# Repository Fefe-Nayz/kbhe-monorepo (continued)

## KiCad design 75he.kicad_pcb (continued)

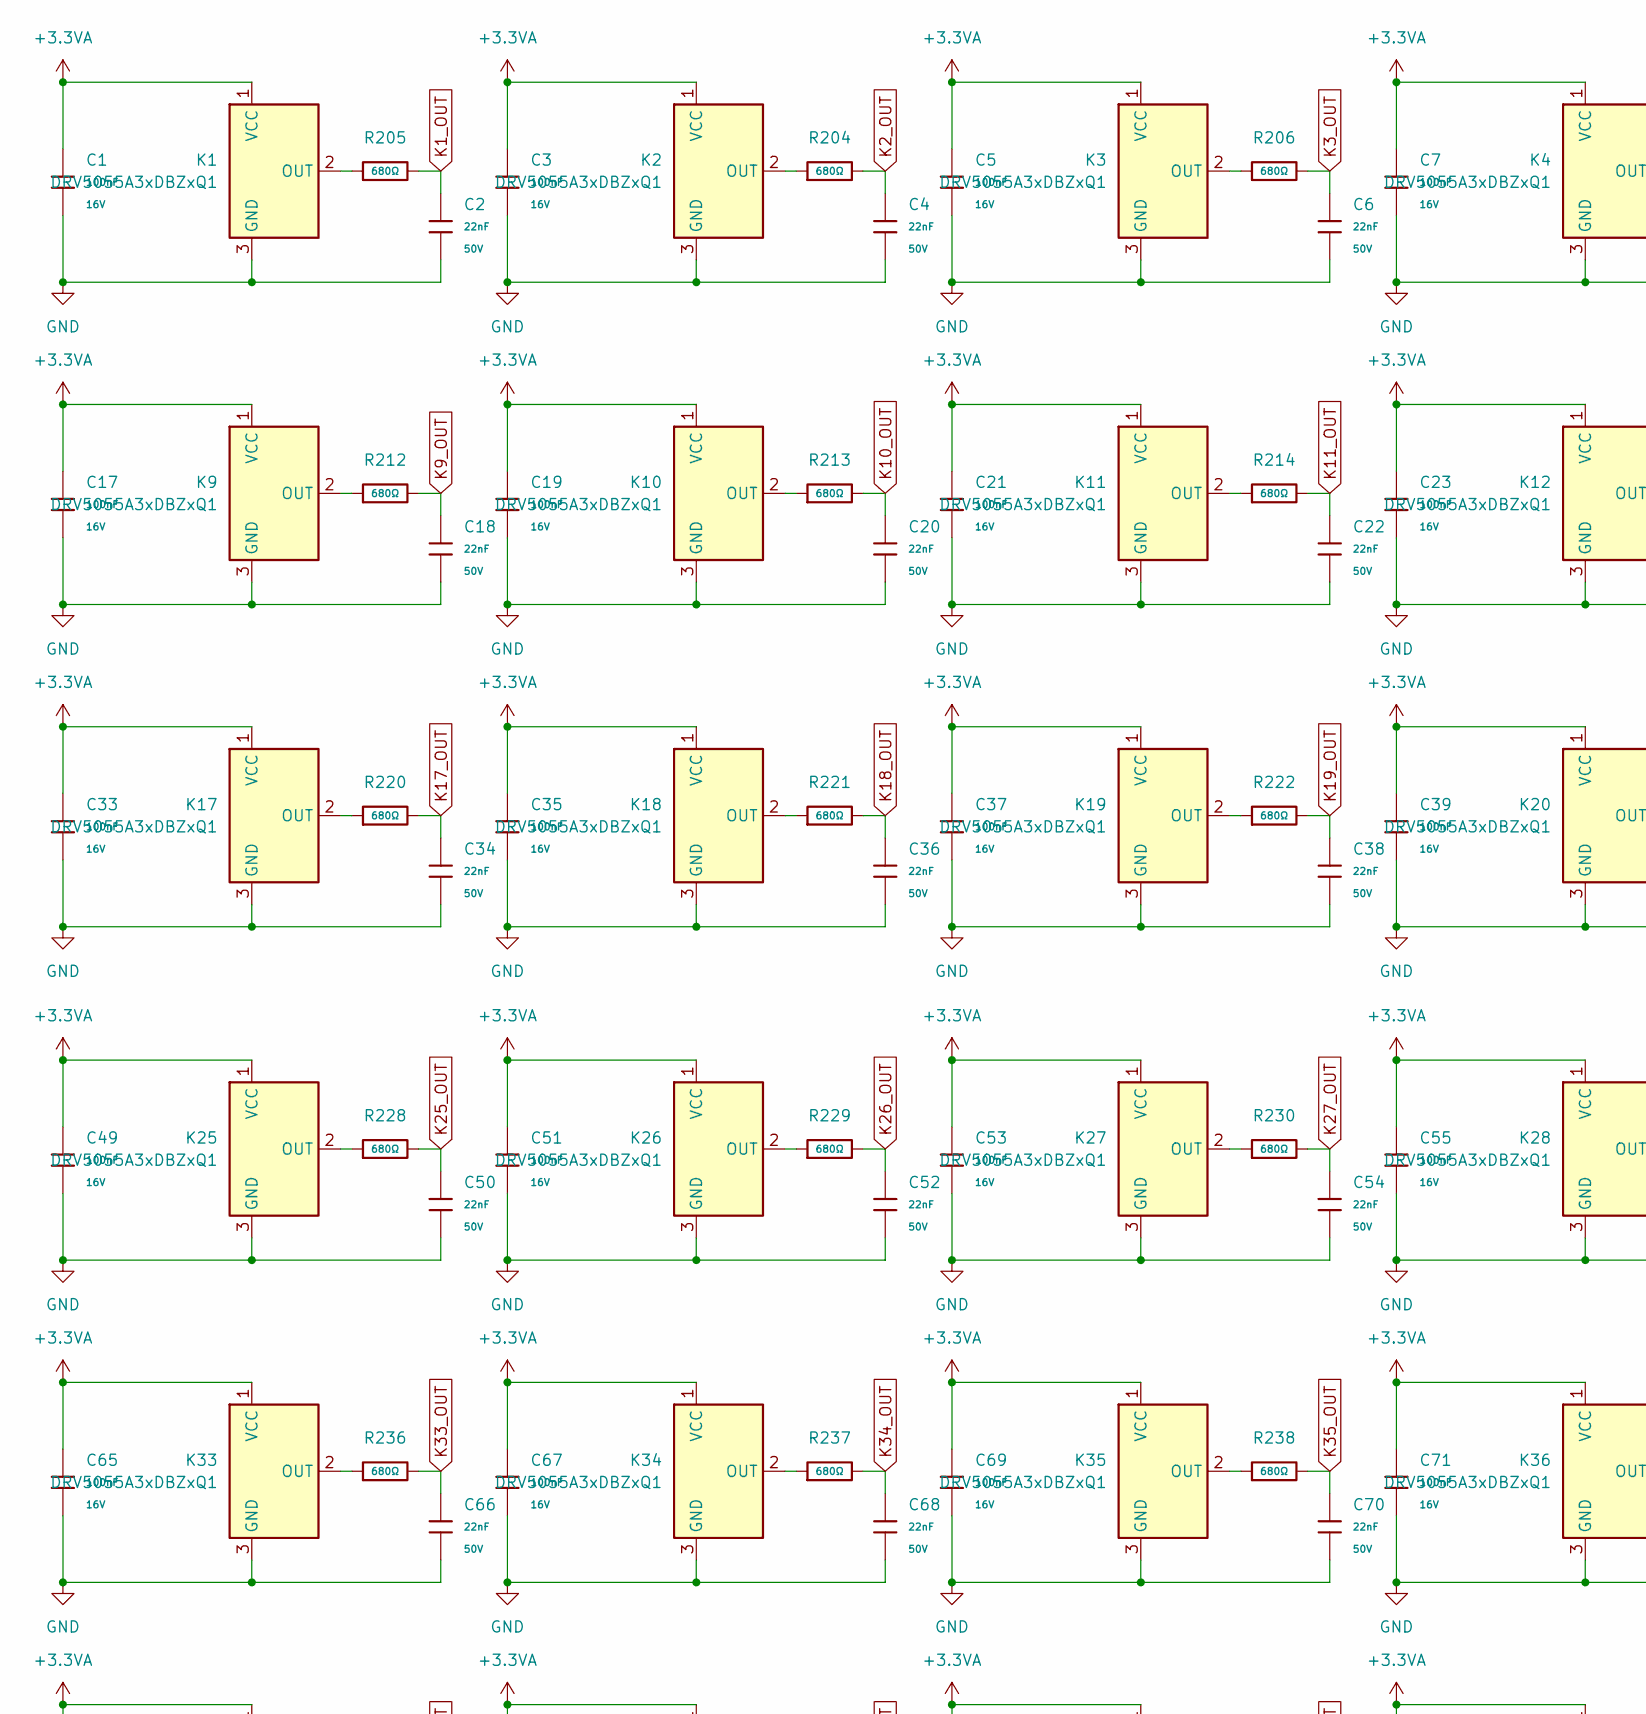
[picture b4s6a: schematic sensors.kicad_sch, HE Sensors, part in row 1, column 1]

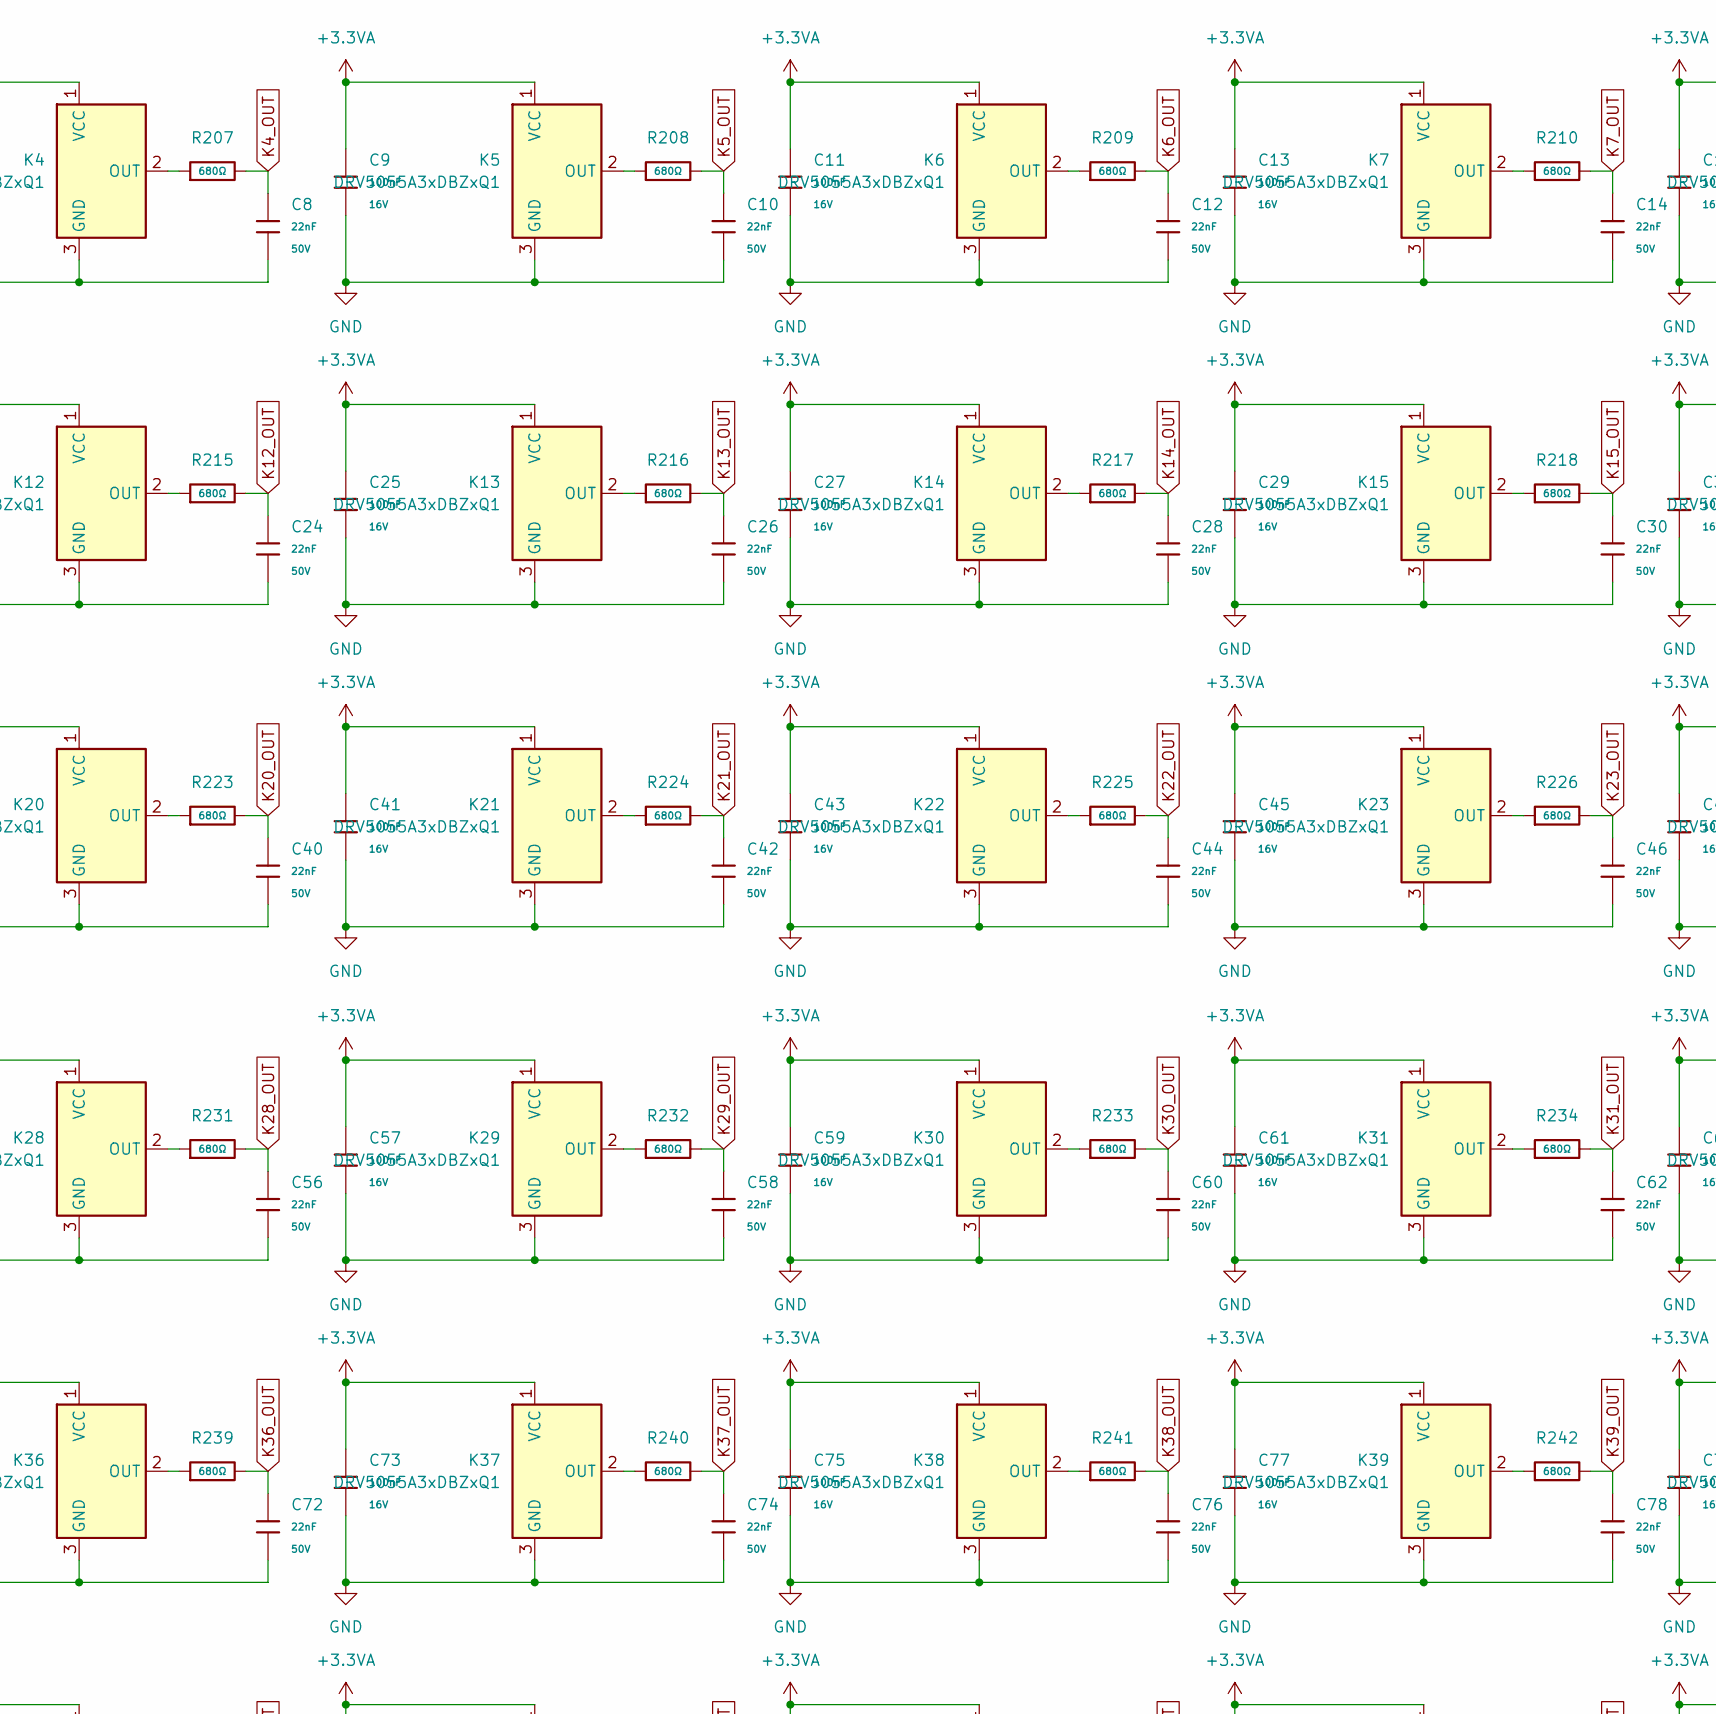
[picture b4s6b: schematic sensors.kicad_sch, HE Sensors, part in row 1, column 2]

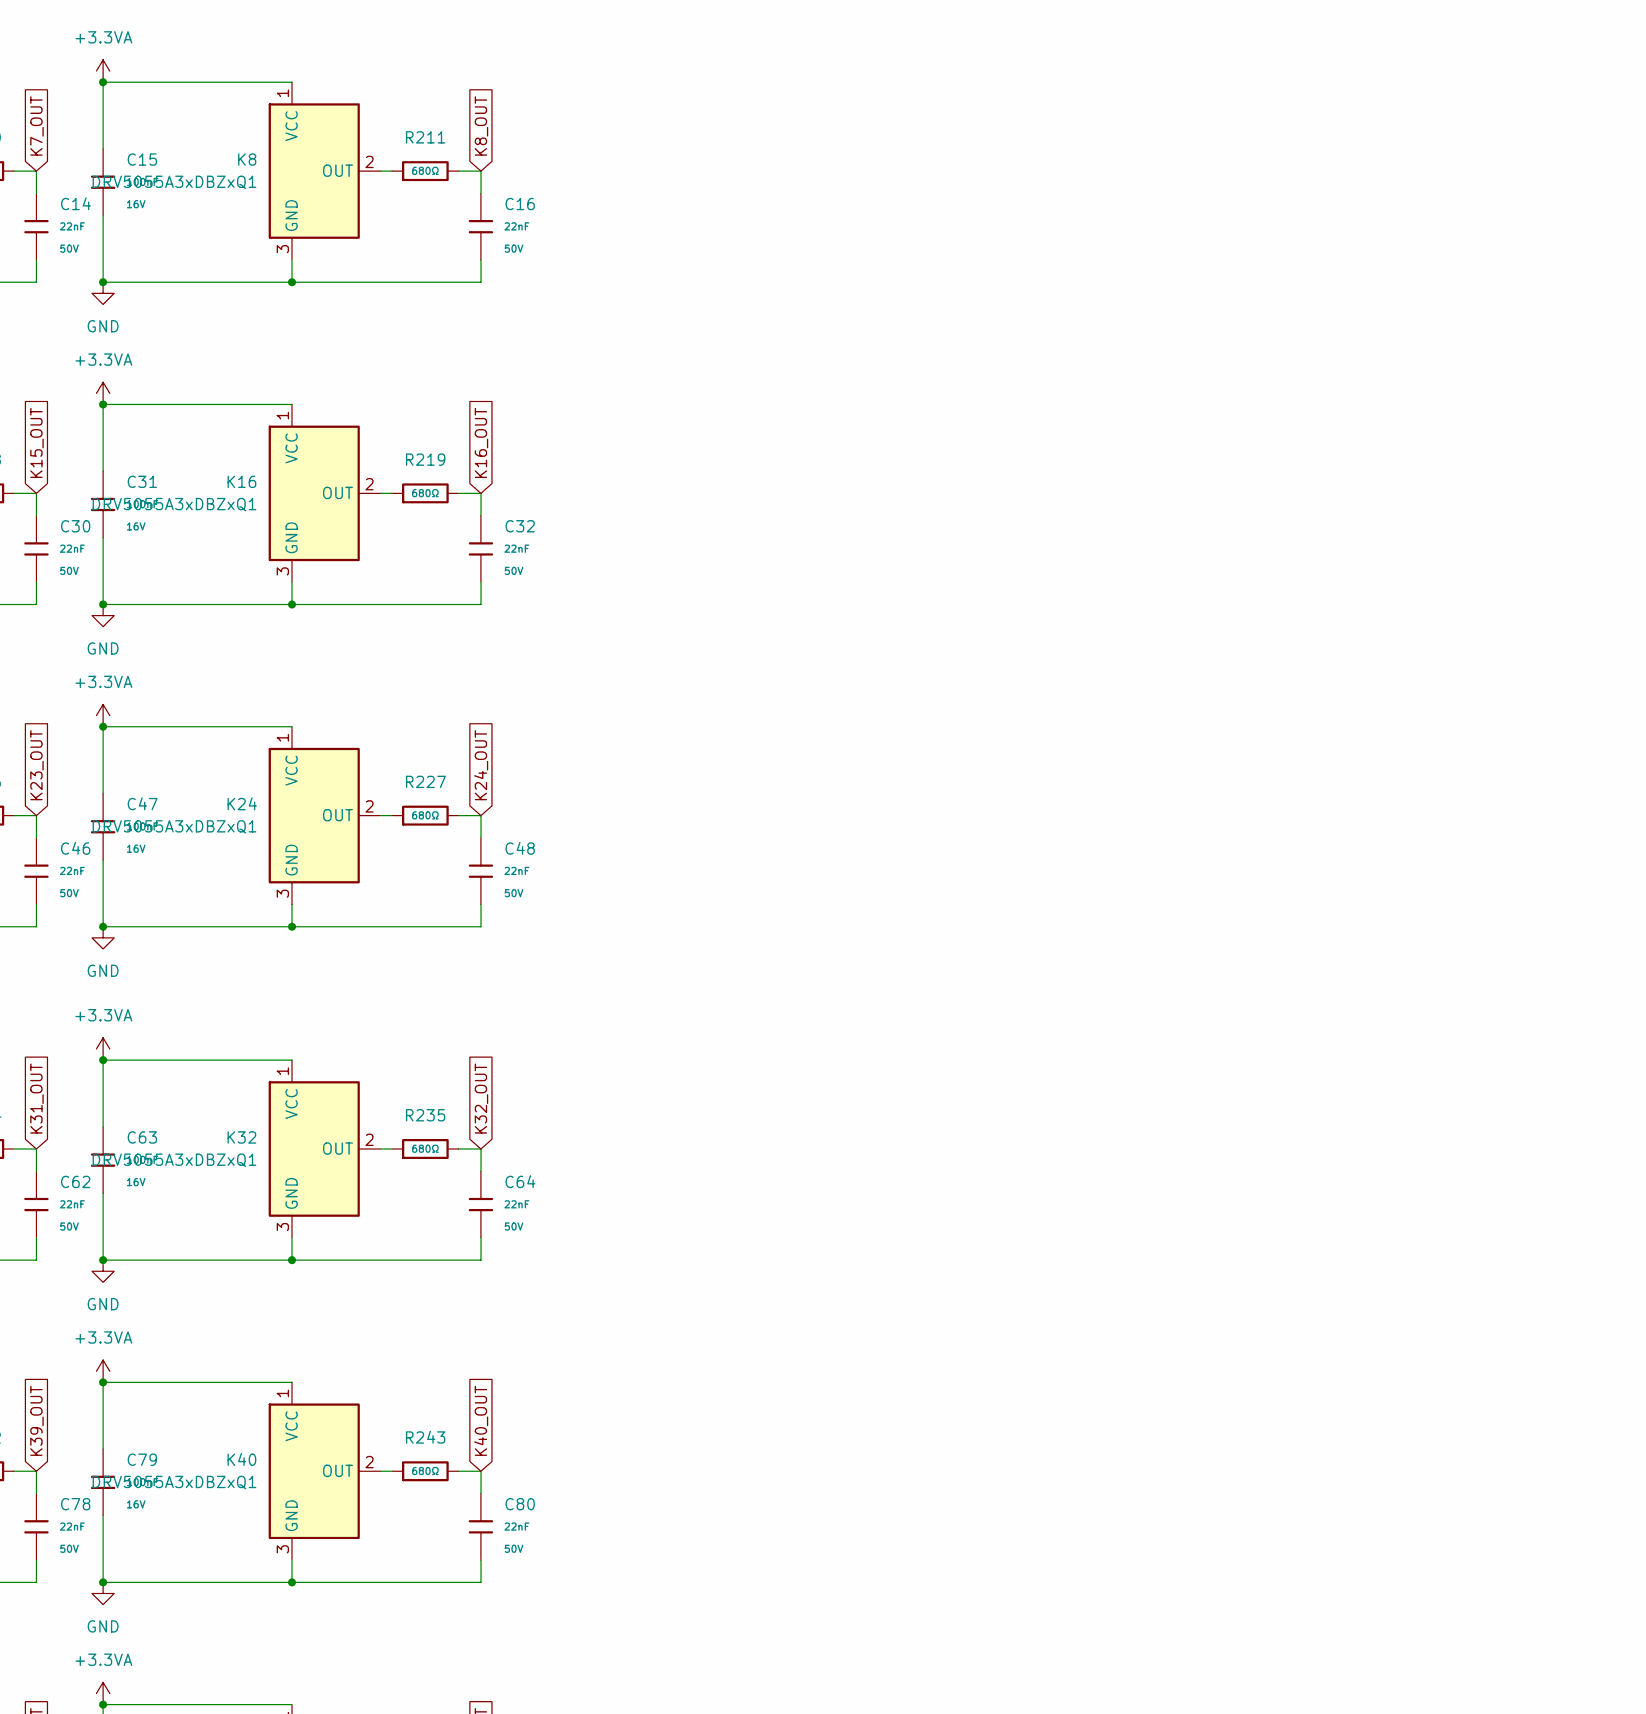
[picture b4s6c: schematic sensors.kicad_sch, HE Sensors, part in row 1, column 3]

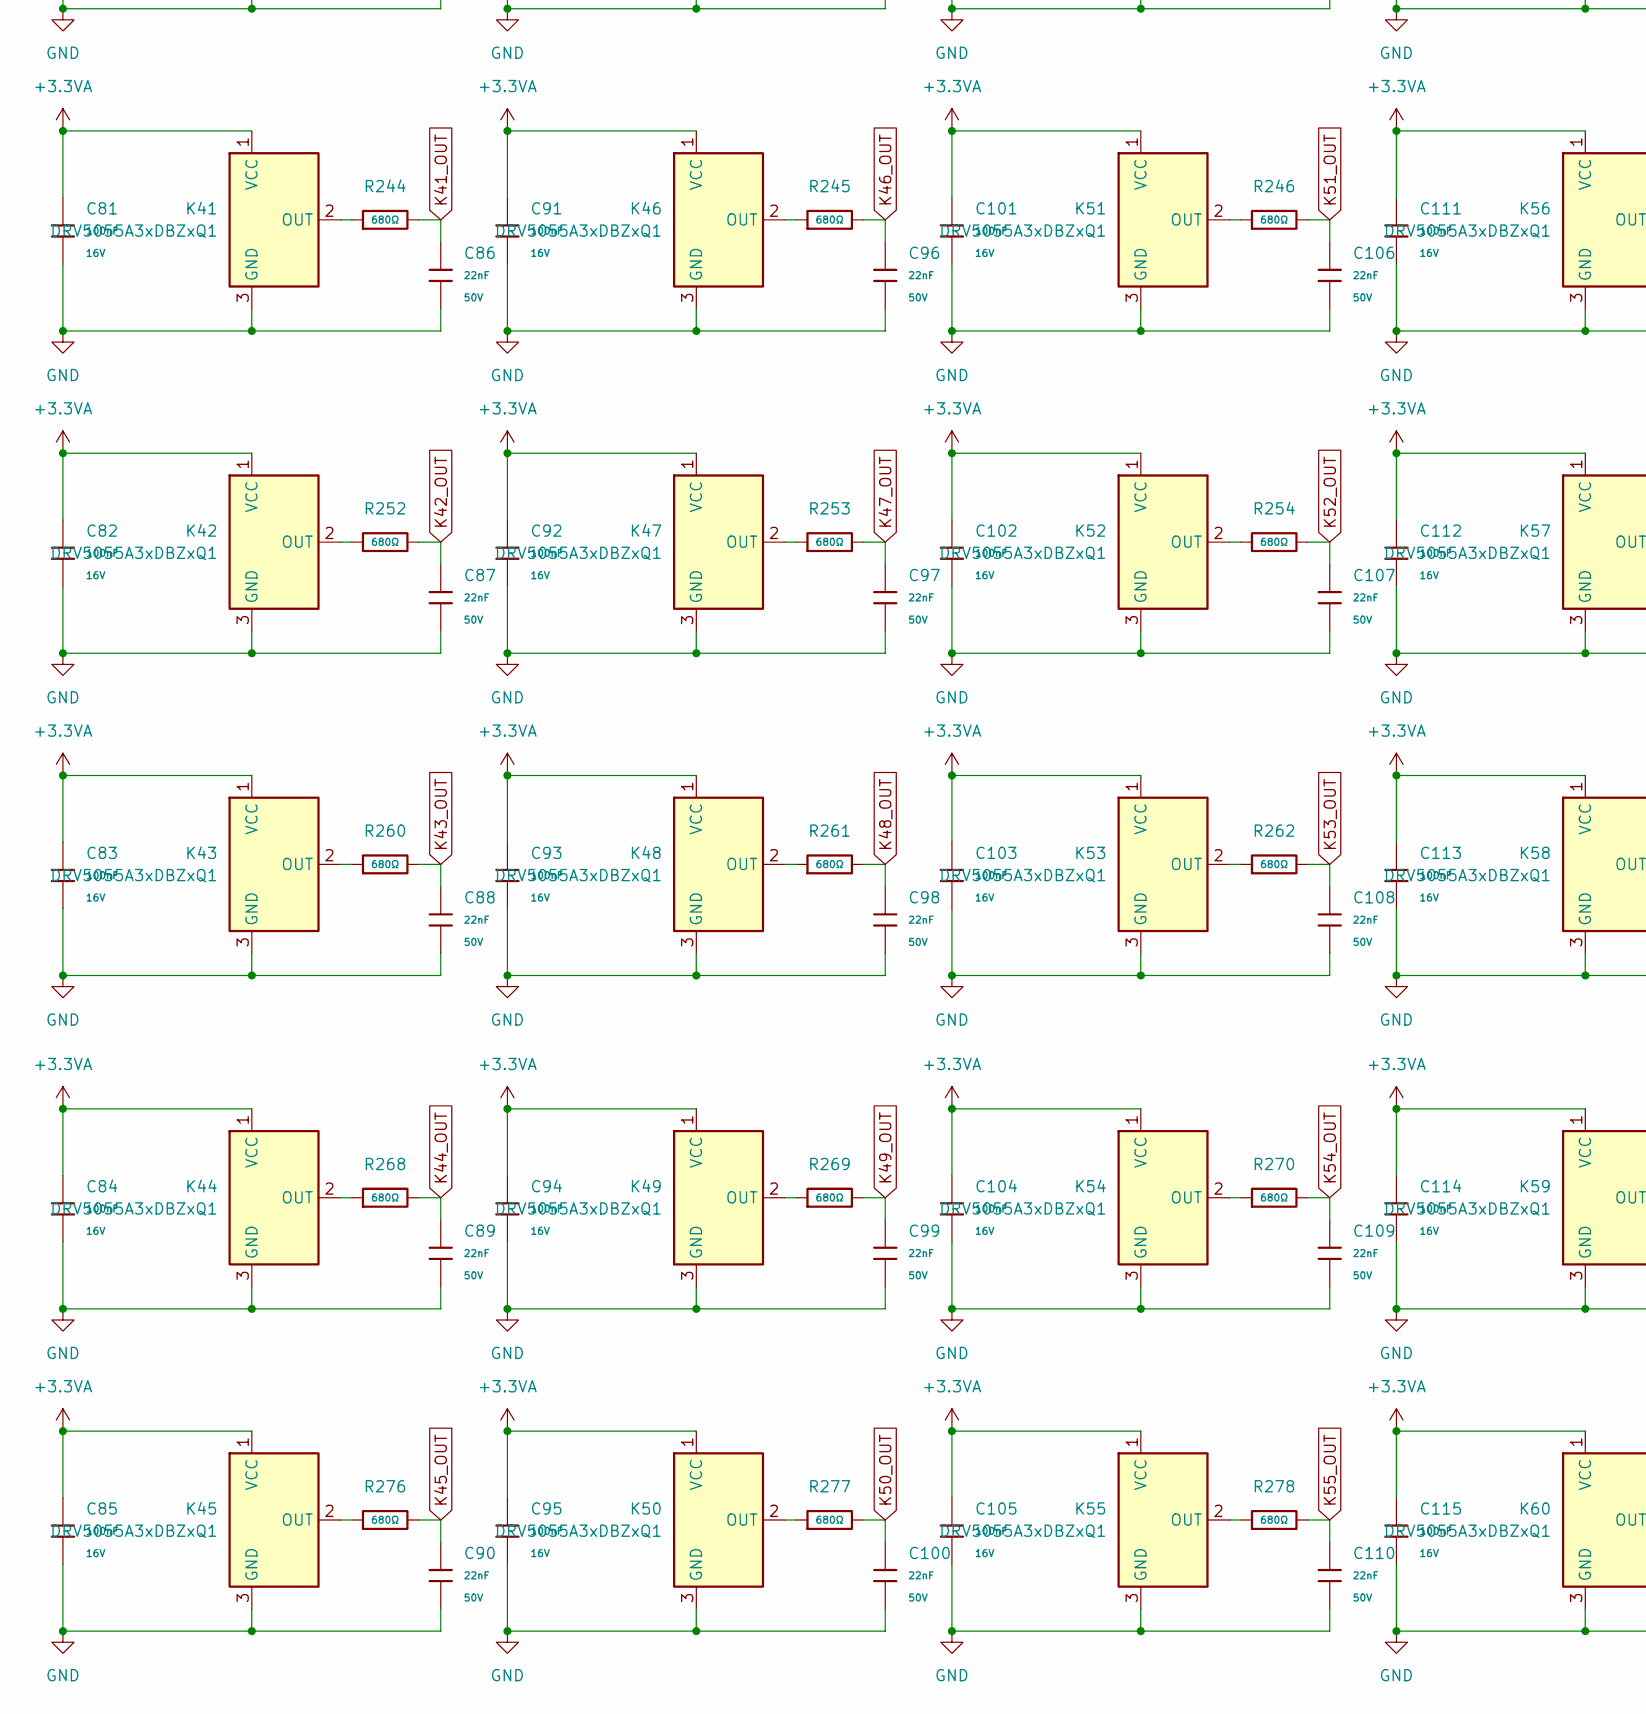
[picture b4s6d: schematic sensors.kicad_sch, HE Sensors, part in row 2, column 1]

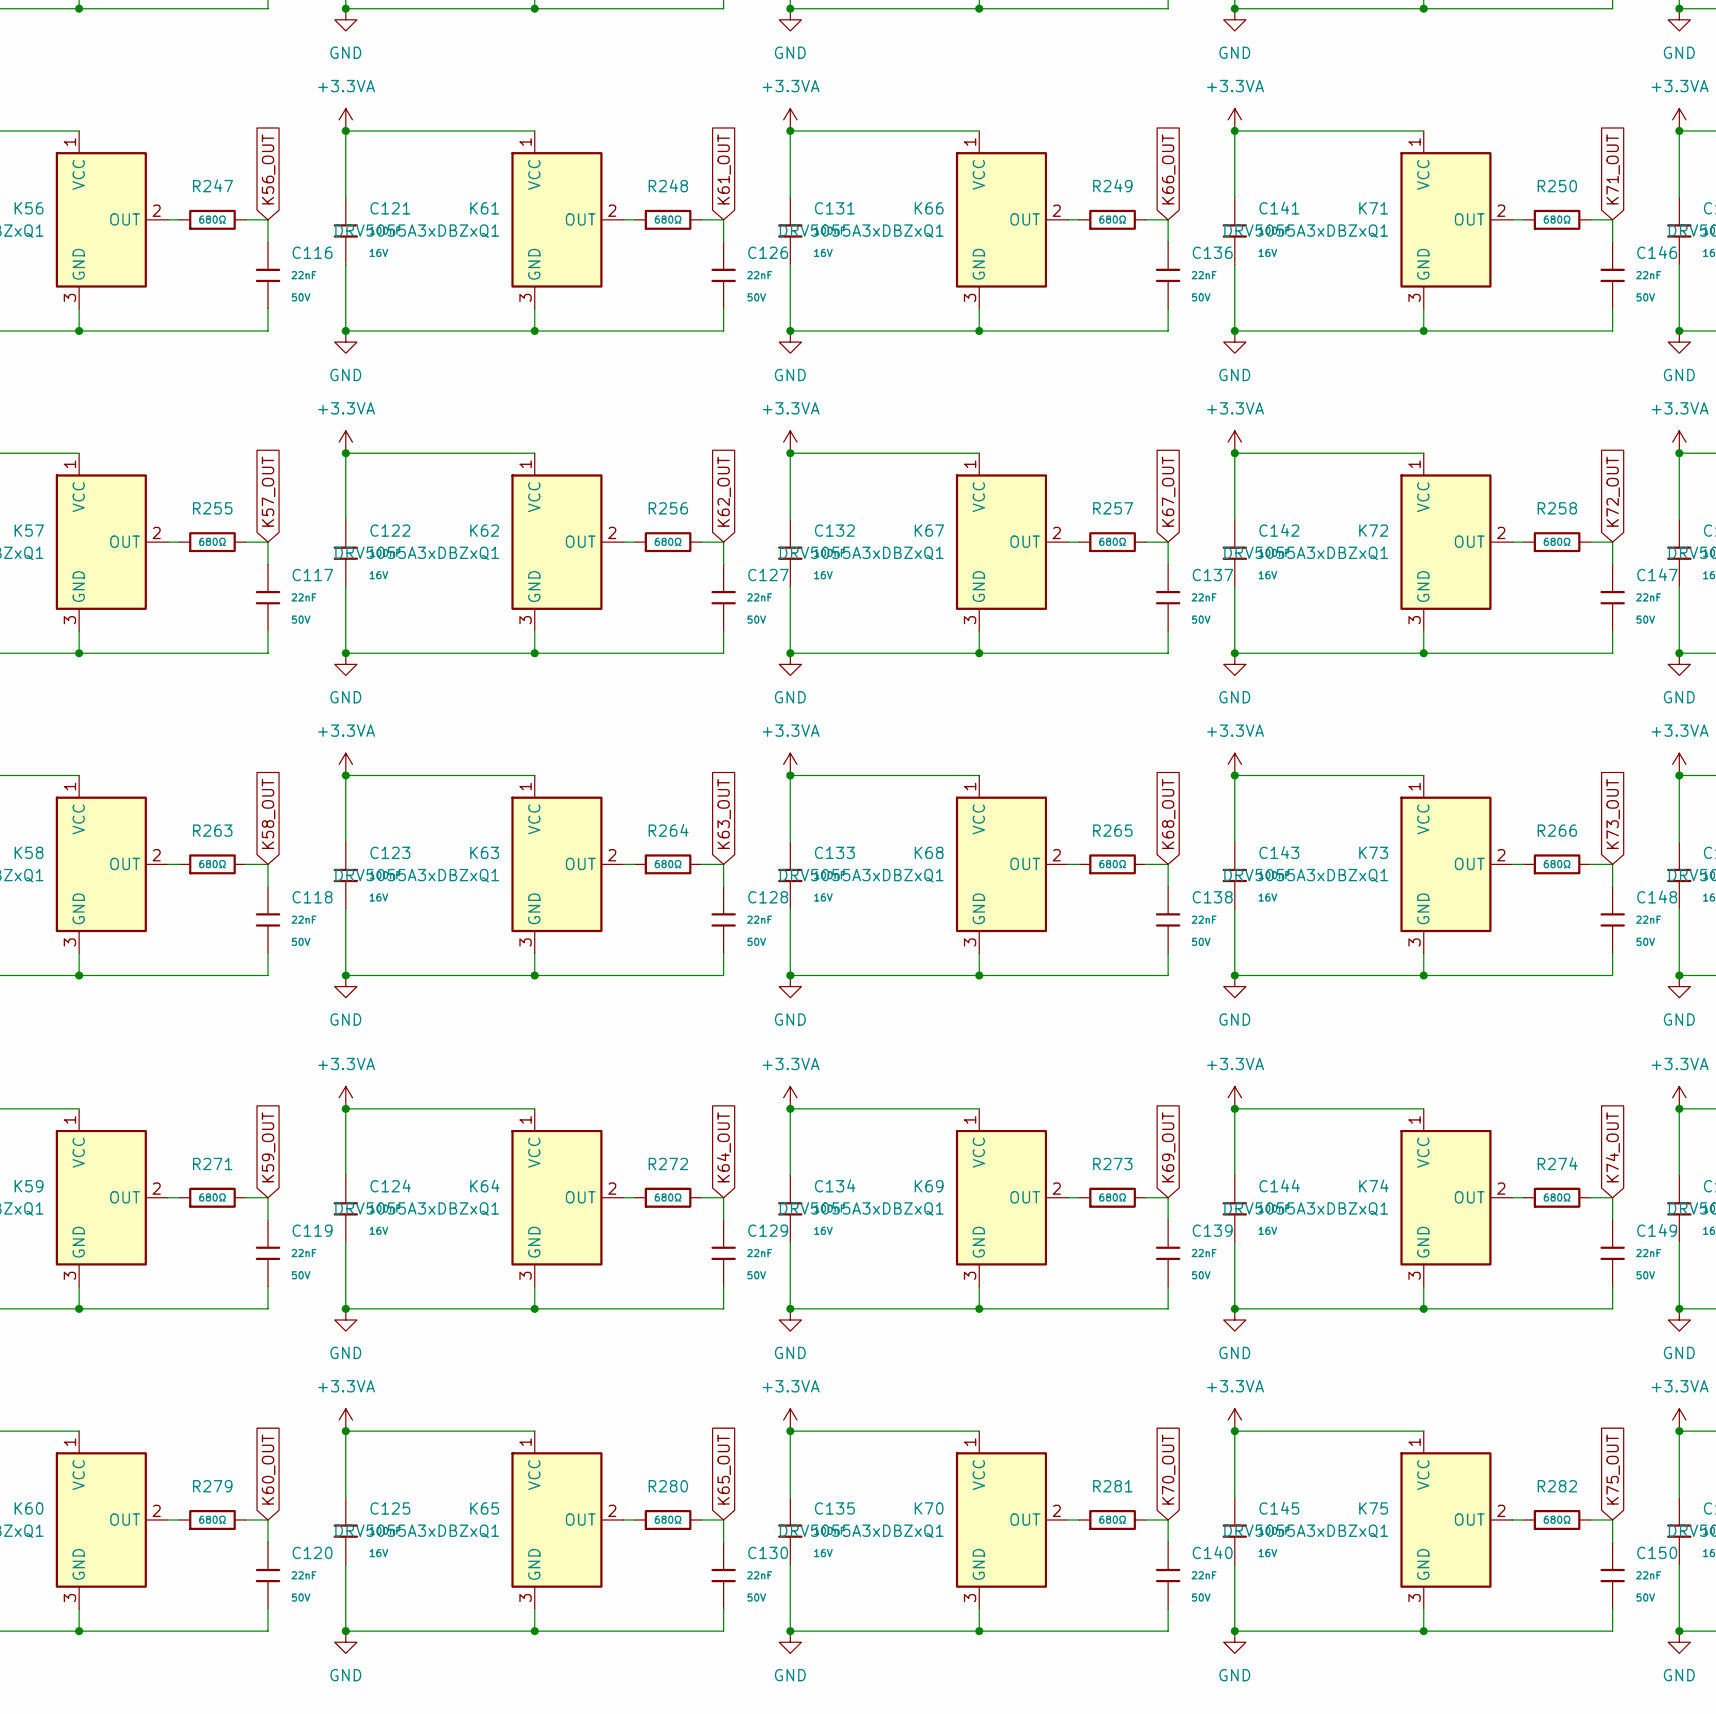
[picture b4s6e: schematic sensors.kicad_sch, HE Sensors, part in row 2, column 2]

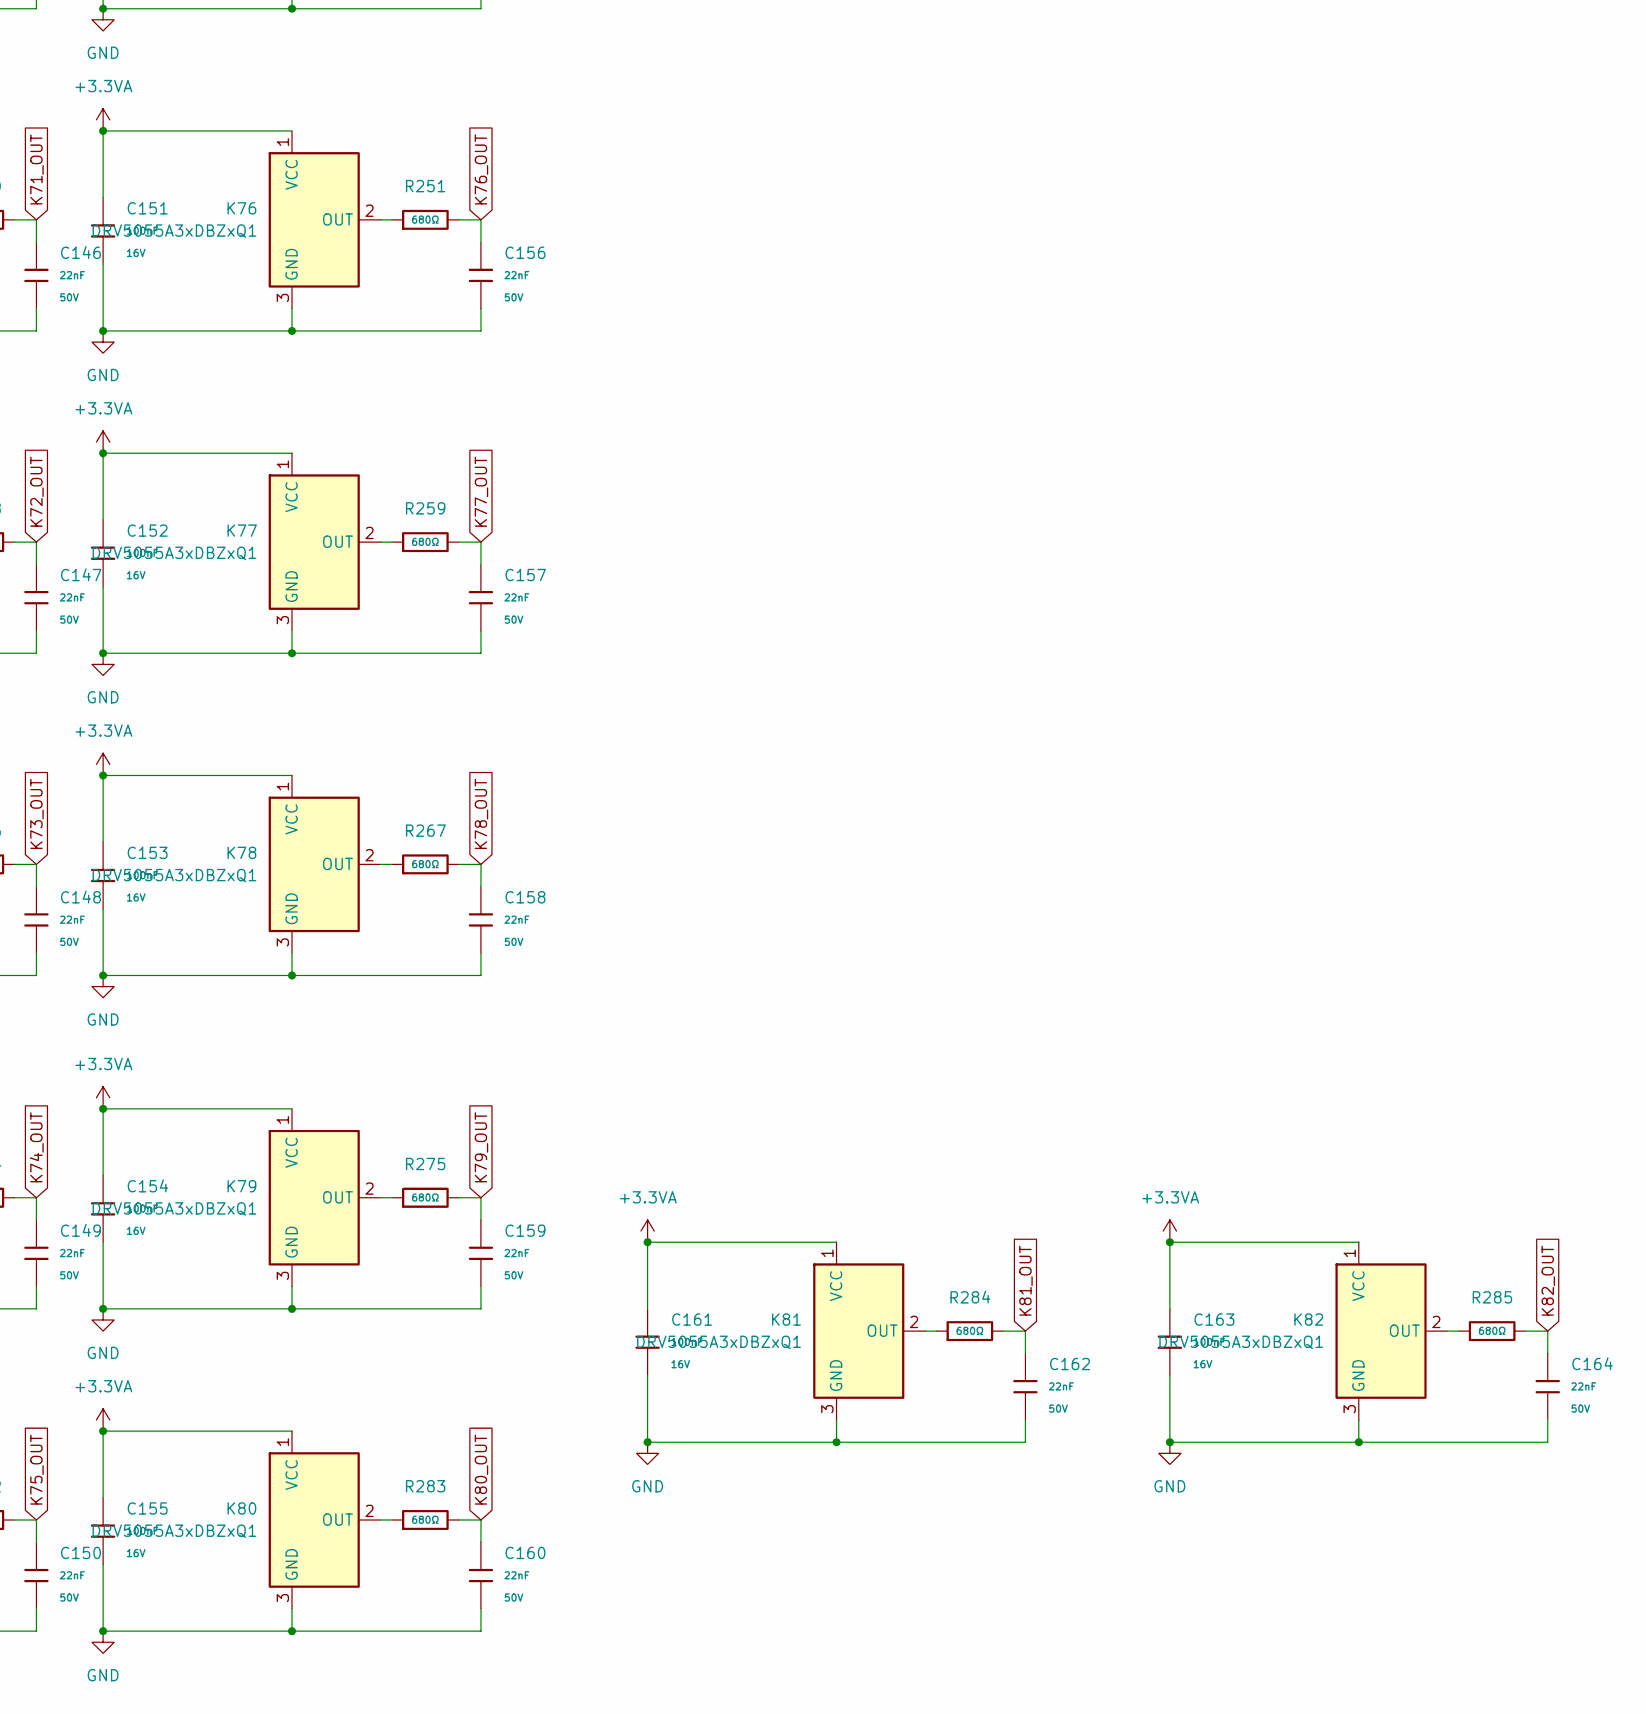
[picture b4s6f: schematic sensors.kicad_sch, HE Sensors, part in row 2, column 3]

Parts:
C1, C3, C5, C7, C9, C11, C13, C15, C17, C19, C21, C23, C25, C27, C29, C31, C33, C35, C37, C39, C41, C43, C45, C47, C49, C51, C53, C55, C57, C59, C61, C63, C65, C67, C69, C71, C73, C75, C77, C79, C81, C82, C83, C84, C85, C91, C92, C93, C94, C95, C101, C102, C103, C104, C105, C111, C112, C113, C114, C115, C121, C122, C123, C124, C125, C131, C132, C133, C134, C135, C141, C142, C143, C144, C145, C151, C152, C153, C154, C155, C161, C163: 100nF; C_0402; Voltage Rated 16V; Tolerance ±10%; Part CL05B104KO5NNNC; LCSC C1525
C2, C4, C6, C8, C10, C12, C14, C16, C18, C20, C22, C24, C26, C28, C30, C32, C34, C36, C38, C40, C42, C44, C46, C48, C50, C52, C54, C56, C58, C60, C62, C64, C66, C68, C70, C72, C74, C76, C78, C80, C86, C87, C88, C89, C90, C96, C97, C98, C99, C100, C106, C107, C108, C109, C110, C116, C117, C118, C119, C120, C126, C127, C128, C129, C130, C136, C137, C138, C139, C140, C146, C147, C148, C149, C150, C156, C157, C158, C159, C160, C162, C164: 22nF; C_0402; Voltage Rated 50V; Tolerance ±10%; Part 0402B223K500NT; LCSC C1532
K1, K2, K3, K4, K5, K6, K7, K8, K9, K10, K11, K12, K13, K14, K15, K16, K17, K18, K19, K20, K21, K22, K23, K24, K25, K26, K27, K28, K29, K30, K31, K32, K33, K34, K35, K36, K37, K38, K39, K40, K41, K42, K43, K44, K45, K46, K47, K48, K49, K50, K51, K52, K53, K54, K55, K56, K57, K58, K59, K60, K61, K62, K63, K64, K65, K66, K67, K68, K69, K70, K71, K72, K73, K74, K75, K76, K77, K78, K79, K80, K81, K82: DRV5055A3xDBZxQ1; SOT-23
R204, R205, R206, R207, R208, R209, R210, R211, R212, R213, R214, R215, R216, R217, R218, R219, R220, R221, R222, R223, R224, R225, R226, R227, R228, R229, R230, R231, R232, R233, R234, R235, R236, R237, R238, R239, R240, R241, R242, R243, R244, R245, R246, R247, R248, R249, R250, R251, R252, R253, R254, R255, R256, R257, R258, R259, R260, R261, R262, R263, R264, R265, R266, R267, R268, R269, R270, R271, R272, R273, R274, R275, R276, R277, R278, R279, R280, R281, R282, R283, R284, R285: 680Ω; R_0402; Overload Voltage (Max) 50V; Tolerance ±1%; Part 0402WGF6800TCE; LCSC C25130

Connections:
+3.3VA: C1.2, C3.2, C5.2, C7.2, C9.2, C11.2, C13.2, C15.2, C17.2, C19.2, C21.2, C23.2, C25.2, C27.2, C29.2, C31.2, C33.2, C35.2, C37.2, C39.2, C41.2, C43.2, C45.2, C47.2, C49.2, C51.2, C53.2, C55.2, C57.2, C59.2, C61.2, C63.2, C65.2, C67.2, C69.2, C71.2, C73.2, C75.2, C77.2, C79.2, C81.2, C82.2, C83.2, C84.2, C85.2, C91.2, C92.2, C93.2, C94.2, C95.2, C101.2, C102.2, C103.2, C104.2, C105.2, C111.2, C112.2, C113.2, C114.2, C115.2, C121.2, C122.2, C123.2, C124.2, C125.2, C131.2, C132.2, C133.2, C134.2, C135.2, C141.2, C142.2, C143.2, C144.2, C145.2, C151.2, C152.2, C153.2, C154.2, C155.2, C161.2, C163.2, K1.1 (VCC), K2.1 (VCC), K3.1 (VCC), K4.1 (VCC), K5.1 (VCC), K6.1 (VCC), K7.1 (VCC), K8.1 (VCC), K9.1 (VCC), K10.1 (VCC), K11.1 (VCC), K12.1 (VCC), K13.1 (VCC), K14.1 (VCC), K15.1 (VCC), K16.1 (VCC), K17.1 (VCC), K18.1 (VCC), K19.1 (VCC), K20.1 (VCC), K21.1 (VCC), K22.1 (VCC), K23.1 (VCC), K24.1 (VCC), K25.1 (VCC), K26.1 (VCC), K27.1 (VCC), K28.1 (VCC), K29.1 (VCC), K30.1 (VCC), K31.1 (VCC), K32.1 (VCC), K33.1 (VCC), K34.1 (VCC), K35.1 (VCC), K36.1 (VCC), K37.1 (VCC), K38.1 (VCC), K39.1 (VCC), K40.1 (VCC), K41.1 (VCC), K42.1 (VCC), K43.1 (VCC), K44.1 (VCC), K45.1 (VCC), K46.1 (VCC), K47.1 (VCC), K48.1 (VCC), K49.1 (VCC), K50.1 (VCC), K51.1 (VCC), K52.1 (VCC), K53.1 (VCC), K54.1 (VCC), K55.1 (VCC), K56.1 (VCC), K57.1 (VCC), K58.1 (VCC), K59.1 (VCC), K60.1 (VCC), K61.1 (VCC), K62.1 (VCC), K63.1 (VCC), K64.1 (VCC), K65.1 (VCC), K66.1 (VCC), K67.1 (VCC), K68.1 (VCC), K69.1 (VCC), K70.1 (VCC), K71.1 (VCC), K72.1 (VCC), K73.1 (VCC), K74.1 (VCC), K75.1 (VCC), K76.1 (VCC), K77.1 (VCC), K78.1 (VCC), K79.1 (VCC), K80.1 (VCC), K81.1 (VCC), K82.1 (VCC); also elsewhere on the board
GND: C1.1, C2.1, C3.1, C4.1, C5.1, C6.1, C7.1, C8.1, C9.1, C10.1, C11.1, C12.1, C13.1, C14.1, C15.1, C16.1, C17.1, C18.1, C19.1, C20.1, C21.1, C22.1, C23.1, C24.1, C25.1, C26.1, C27.1, C28.1, C29.1, C30.1, C31.1, C32.1, C33.1, C34.1, C35.1, C36.1, C37.1, C38.1, C39.1, C40.1, C41.1, C42.1, C43.1, C44.1, C45.1, C46.1, C47.1, C48.1, C49.1, C50.1, C51.1, C52.1, C53.1, C54.1, C55.1, C56.1, C57.1, C58.1, C59.1, C60.1, C61.1, C62.1, C63.1, C64.1, C65.1, C66.1, C67.1, C68.1, C69.1, C70.1, C71.1, C72.1, C73.1, C74.1, C75.1, C76.1, C77.1, C78.1, C79.1, C80.1, C81.1, C82.1, C83.1, C84.1, C85.1, C86.1, C87.1, C88.1, C89.1, C90.1, C91.1, C92.1, C93.1, C94.1, C95.1, C96.1, C97.1, C98.1, C99.1, C100.1, C101.1, C102.1, C103.1, C104.1, C105.1, C106.1, C107.1, C108.1, C109.1, C110.1, C111.1, C112.1, C113.1, C114.1, C115.1, C116.1, C117.1, C118.1, C119.1, C120.1, C121.1, C122.1, C123.1, C124.1, C125.1, C126.1, C127.1, C128.1, C129.1, C130.1, C131.1, C132.1, C133.1, C134.1, C135.1, C136.1, C137.1, C138.1, C139.1, C140.1, C141.1, C142.1, C143.1, C144.1, C145.1, C146.1, C147.1, C148.1, C149.1, C150.1, C151.1, C152.1, C153.1, C154.1, C155.1, C156.1, C157.1, C158.1, C159.1, C160.1, C161.1, C162.1, C163.1, C164.1, K1.3 (GND), K2.3 (GND), K3.3 (GND), K4.3 (GND), K5.3 (GND), K6.3 (GND), K7.3 (GND), K8.3 (GND), K9.3 (GND), K10.3 (GND), K11.3 (GND), K12.3 (GND), K13.3 (GND), K14.3 (GND), K15.3 (GND), K16.3 (GND), K17.3 (GND), K18.3 (GND), K19.3 (GND), K20.3 (GND), K21.3 (GND), K22.3 (GND), K23.3 (GND), K24.3 (GND), K25.3 (GND), K26.3 (GND), K27.3 (GND), K28.3 (GND), K29.3 (GND), K30.3 (GND), K31.3 (GND), K32.3 (GND), K33.3 (GND), K34.3 (GND), K35.3 (GND), K36.3 (GND), K37.3 (GND), K38.3 (GND), K39.3 (GND), K40.3 (GND), K41.3 (GND), K42.3 (GND), K43.3 (GND), K44.3 (GND), K45.3 (GND), K46.3 (GND), K47.3 (GND), K48.3 (GND), K49.3 (GND), K50.3 (GND), K51.3 (GND), K52.3 (GND), K53.3 (GND), K54.3 (GND), K55.3 (GND), K56.3 (GND), K57.3 (GND), K58.3 (GND), K59.3 (GND), K60.3 (GND), K61.3 (GND), K62.3 (GND), K63.3 (GND), K64.3 (GND), K65.3 (GND), K66.3 (GND), K67.3 (GND), K68.3 (GND), K69.3 (GND), K70.3 (GND), K71.3 (GND), K72.3 (GND), K73.3 (GND), K74.3 (GND), K75.3 (GND), K76.3 (GND), K77.3 (GND), K78.3 (GND)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; also elsewhere on the board
K1_OUT: C2.2, R205.2; also elsewhere on the board
K2_OUT: C4.2, R204.2; also elsewhere on the board
K3_OUT: C6.2, R206.2; also elsewhere on the board
K4_OUT: C8.2, R207.2; also elsewhere on the board
K5_OUT: C10.2, R208.2; also elsewhere on the board
K6_OUT: C12.2, R209.2; also elsewhere on the board
K7_OUT: C14.2, R210.2; also elsewhere on the board
K8_OUT: C16.2, R211.2; also elsewhere on the board
K9_OUT: C18.2, R212.2; also elsewhere on the board
K10_OUT: C20.2, R213.2; also elsewhere on the board
K11_OUT: C22.2, R214.2; also elsewhere on the board
K12_OUT: C24.2, R215.2; also elsewhere on the board
K13_OUT: C26.2, R216.2; also elsewhere on the board
K14_OUT: C28.2, R217.2; also elsewhere on the board
K15_OUT: C30.2, R218.2; also elsewhere on the board
K16_OUT: C32.2, R219.2; also elsewhere on the board
K17_OUT: C34.2, R220.2; also elsewhere on the board
K18_OUT: C36.2, R221.2; also elsewhere on the board
K19_OUT: C38.2, R222.2; also elsewhere on the board
K20_OUT: C40.2, R223.2; also elsewhere on the board
K21_OUT: C42.2, R224.2; also elsewhere on the board
K22_OUT: C44.2, R225.2; also elsewhere on the board
K23_OUT: C46.2, R226.2; also elsewhere on the board
K24_OUT: C48.2, R227.2; also elsewhere on the board
K25_OUT: C50.2, R228.2; also elsewhere on the board
K26_OUT: C52.2, R229.2; also elsewhere on the board
K27_OUT: C54.2, R230.2; also elsewhere on the board
K28_OUT: C56.2, R231.2; also elsewhere on the board
K29_OUT: C58.2, R232.2; also elsewhere on the board
K30_OUT: C60.2, R233.2; also elsewhere on the board
K31_OUT: C62.2, R234.2; also elsewhere on the board
K32_OUT: C64.2, R235.2; also elsewhere on the board
K33_OUT: C66.2, R236.2; also elsewhere on the board
K34_OUT: C68.2, R237.2; also elsewhere on the board
K35_OUT: C70.2, R238.2; also elsewhere on the board
K36_OUT: C72.2, R239.2; also elsewhere on the board
K37_OUT: C74.2, R240.2; also elsewhere on the board
K38_OUT: C76.2, R241.2; also elsewhere on the board
K39_OUT: C78.2, R242.2; also elsewhere on the board
K40_OUT: C80.2, R243.2; also elsewhere on the board
K41_OUT: C86.2, R244.2; also elsewhere on the board
K42_OUT: C87.2, R252.2; also elsewhere on the board
K43_OUT: C88.2, R260.2; also elsewhere on the board
K44_OUT: C89.2, R268.2; also elsewhere on the board
K45_OUT: C90.2, R276.2; also elsewhere on the board
K46_OUT: C96.2, R245.2; also elsewhere on the board
K47_OUT: C97.2, R253.2; also elsewhere on the board
K48_OUT: C98.2, R261.2; also elsewhere on the board
K49_OUT: C99.2, R269.2; also elsewhere on the board
K50_OUT: C100.2, R277.2; also elsewhere on the board
K51_OUT: C106.2, R246.2; also elsewhere on the board
K52_OUT: C107.2, R254.2; also elsewhere on the board
K53_OUT: C108.2, R262.2; also elsewhere on the board
K54_OUT: C109.2, R270.2; also elsewhere on the board
K55_OUT: C110.2, R278.2; also elsewhere on the board
K56_OUT: C116.2, R247.2; also elsewhere on the board
K57_OUT: C117.2, R255.2; also elsewhere on the board
K58_OUT: C118.2, R263.2; also elsewhere on the board
K59_OUT: C119.2, R271.2; also elsewhere on the board
K60_OUT: C120.2, R279.2; also elsewhere on the board
K61_OUT: C126.2, R248.2; also elsewhere on the board
K62_OUT: C127.2, R256.2; also elsewhere on the board
K63_OUT: C128.2, R264.2; also elsewhere on the board
K64_OUT: C129.2, R272.2; also elsewhere on the board
K65_OUT: C130.2, R280.2; also elsewhere on the board
K66_OUT: C136.2, R249.2; also elsewhere on the board
K67_OUT: C137.2, R257.2; also elsewhere on the board
K68_OUT: C138.2, R265.2; also elsewhere on the board
K69_OUT: C139.2, R273.2; also elsewhere on the board
K70_OUT: C140.2, R281.2; also elsewhere on the board
K71_OUT: C146.2, R250.2; also elsewhere on the board
K72_OUT: C147.2, R258.2; also elsewhere on the board
K73_OUT: C148.2, R266.2; also elsewhere on the board
K74_OUT: C149.2, R274.2; also elsewhere on the board
K75_OUT: C150.2, R282.2; also elsewhere on the board
K76_OUT: C156.2, R251.2; also elsewhere on the board
K77_OUT: C157.2, R259.2; also elsewhere on the board
K78_OUT: C158.2, R267.2; also elsewhere on the board
K79_OUT: C159.2, R275.2; also elsewhere on the board
K80_OUT: C160.2, R283.2; also elsewhere on the board
K81_OUT: C162.2, R284.2; also elsewhere on the board
K82_OUT: C164.2, R285.2; also elsewhere on the board
unnamed: K1.2 (OUT), R205.1
unnamed: K2.2 (OUT), R204.1
unnamed: K3.2 (OUT), R206.1
unnamed: K4.2 (OUT), R207.1
unnamed: K5.2 (OUT), R208.1
unnamed: K6.2 (OUT), R209.1
unnamed: K7.2 (OUT), R210.1
unnamed: K8.2 (OUT), R211.1
unnamed: K9.2 (OUT), R212.1
unnamed: K10.2 (OUT), R213.1
unnamed: K11.2 (OUT), R214.1
unnamed: K12.2 (OUT), R215.1
unnamed: K13.2 (OUT), R216.1
unnamed: K14.2 (OUT), R217.1
unnamed: K15.2 (OUT), R218.1
unnamed: K16.2 (OUT), R219.1
unnamed: K17.2 (OUT), R220.1
unnamed: K18.2 (OUT), R221.1
unnamed: K19.2 (OUT), R222.1
unnamed: K20.2 (OUT), R223.1
unnamed: K21.2 (OUT), R224.1
unnamed: K22.2 (OUT), R225.1
unnamed: K23.2 (OUT), R226.1
unnamed: K24.2 (OUT), R227.1
unnamed: K25.2 (OUT), R228.1
unnamed: K26.2 (OUT), R229.1
unnamed: K27.2 (OUT), R230.1
unnamed: K28.2 (OUT), R231.1
unnamed: K29.2 (OUT), R232.1
unnamed: K30.2 (OUT), R233.1
unnamed: K31.2 (OUT), R234.1
unnamed: K32.2 (OUT), R235.1
unnamed: K33.2 (OUT), R236.1
unnamed: K34.2 (OUT), R237.1
unnamed: K35.2 (OUT), R238.1
unnamed: K36.2 (OUT), R239.1
unnamed: K37.2 (OUT), R240.1
unnamed: K38.2 (OUT), R241.1
unnamed: K39.2 (OUT), R242.1
unnamed: K40.2 (OUT), R243.1
unnamed: K41.2 (OUT), R244.1
unnamed: K42.2 (OUT), R252.1
unnamed: K43.2 (OUT), R260.1
unnamed: K44.2 (OUT), R268.1
unnamed: K45.2 (OUT), R276.1
unnamed: K46.2 (OUT), R245.1
unnamed: K47.2 (OUT), R253.1
unnamed: K48.2 (OUT), R261.1
unnamed: K49.2 (OUT), R269.1
unnamed: K50.2 (OUT), R277.1
unnamed: K51.2 (OUT), R246.1
unnamed: K52.2 (OUT), R254.1
unnamed: K53.2 (OUT), R262.1
unnamed: K54.2 (OUT), R270.1
unnamed: K55.2 (OUT), R278.1
unnamed: K56.2 (OUT), R247.1
unnamed: K57.2 (OUT), R255.1
unnamed: K58.2 (OUT), R263.1
unnamed: K59.2 (OUT), R271.1
unnamed: K60.2 (OUT), R279.1
unnamed: K61.2 (OUT), R248.1
unnamed: K62.2 (OUT), R256.1
unnamed: K63.2 (OUT), R264.1
unnamed: K64.2 (OUT), R272.1
unnamed: K65.2 (OUT), R280.1
unnamed: K66.2 (OUT), R249.1
unnamed: K67.2 (OUT), R257.1
unnamed: K68.2 (OUT), R265.1
unnamed: K69.2 (OUT), R273.1
unnamed: K70.2 (OUT), R281.1
unnamed: K71.2 (OUT), R250.1
unnamed: K72.2 (OUT), R258.1
unnamed: K73.2 (OUT), R266.1
unnamed: K74.2 (OUT), R274.1
unnamed: K75.2 (OUT), R282.1
unnamed: K76.2 (OUT), R251.1
unnamed: K77.2 (OUT), R259.1
unnamed: K78.2 (OUT), R267.1
unnamed: K79.2 (OUT), R275.1
unnamed: K80.2 (OUT), R283.1
unnamed: K81.2 (OUT), R284.1
unnamed: K82.2 (OUT), R285.1
